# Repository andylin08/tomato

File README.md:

# RGB Pomodoro Timer

This is a pocket Pomodoro timer that displays time, date, and motivational quotes using RGB LEDs, dual OLED screens, and Cherry MX switches, all powered by an ESP32-C3. It’s designed to be compact, functional, and visually engaging.

I made this project because I wanted a fun and personal way to stay focused during work sessions. I’ve always liked the tactile feel of mechanical keys and the glow of addressable LEDs, and this felt like a good way to bring them together into something useful. (Also I have like a bunch of unused stickers and I figured I could use them to decorate the case.)

## images

## Bill of Materials (BOM)

| Item                        | Quantity | Approx. Price | Source |
|-----------------------------|----------|----------------|--------|
| ESP32-C3 DevKitM-1          | 1        | $9.40        | [DigiKey](https://www.digikey.com/en/products/detail/espressif-systems/ESP32-C3-DEVKITM-1U/15198974) |
| SK6812 Mini RGB LEDs (20x minimum)| 6  | $2.34         | [AliExpress](https://www.aliexpress.us/item/3256805007401420.html) |
| Cherry MX Switches          | 4        | $0 (alr have them)  | [AliExpress](https://www.aliexpress.us/item/2255800925392137.html) |
| 0.96" I2C OLED Display      | 2        | $4.64 total   | [AliExpress](https://www.aliexpress.us/item/3256804169233174.html) |
| Passive Buzzer              | 1        | $0 (alr have one) | [AliExpress](https://www.aliexpress.us/item/3256807544525574.html) |
| Battery Holder (AAA or 9V) | 1        | $1.01         | [AliExpress](https://www.aliexpress.us/item/3256805982918007.html) |
| Prototype PCB / Custom PCB | 1        | $26.73 (shipping included)  | JLCPCB |
| Total |0| $44.12 (47.20 w tax) | n/a |

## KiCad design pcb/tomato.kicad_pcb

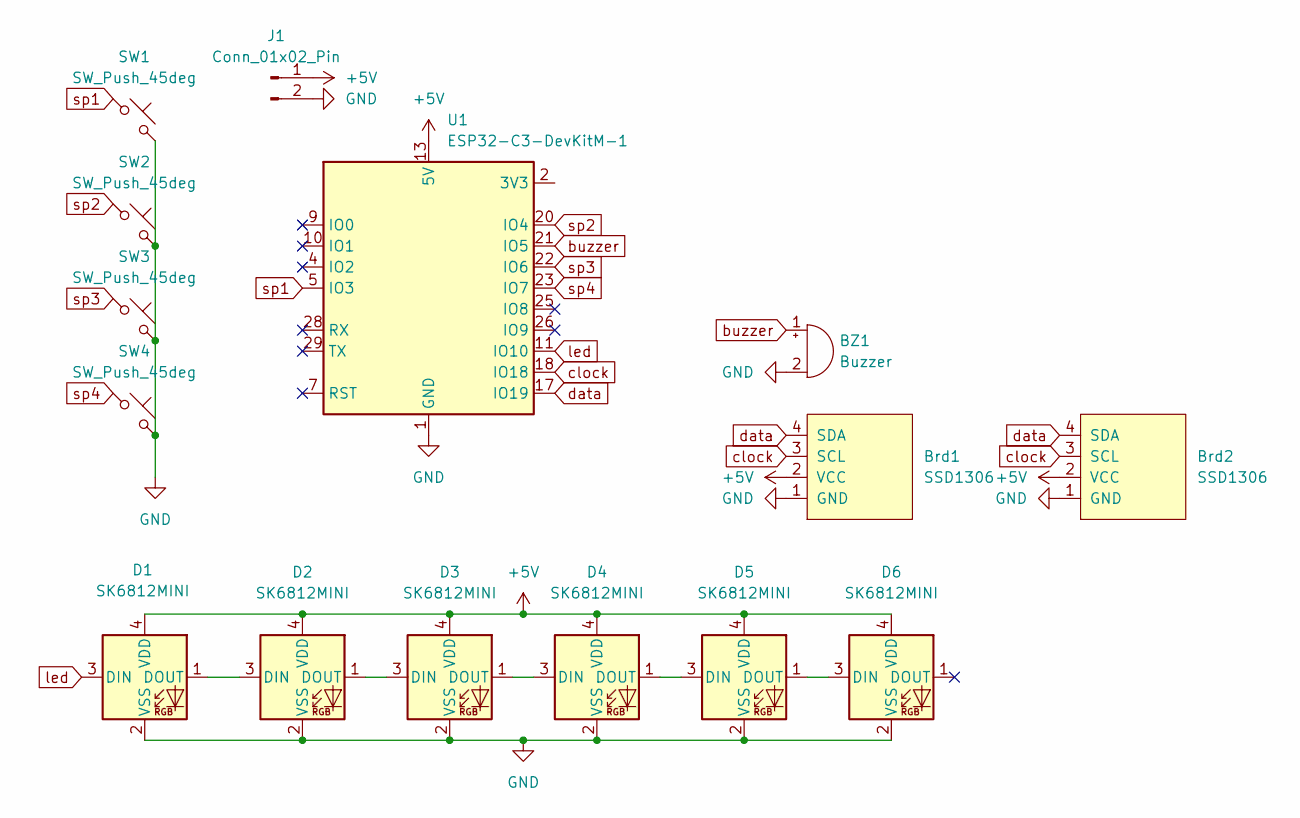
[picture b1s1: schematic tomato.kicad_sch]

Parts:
BZ1: Buzzer; Buzzer_15x7.5RM7.6
Brd1, Brd2: SSD1306; JST_PH_B4B-PH-K_1x04_P2.00mm_Vertical
D1, D2, D3, D4, D5, D6: SK6812MINI; LED_SK6812MINI_PLCC4_3.5x3.5mm_P1.75mm
J1: Conn_01x02_Pin; JST_PH_S2B-PH-K_1x02_P2.00mm_Horizontal
SW1, SW2, SW3, SW4: SW_Push_45deg; SW_Cherry_MX_1.00u_PCB
U1: ESP32-C3-DevKitM-1

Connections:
+5V: Brd1.2 (VCC), Brd2.2 (VCC), D1.4 (VDD), D2.4 (VDD), D3.4 (VDD), D4.4 (VDD), D5.4 (VDD), D6.4 (VDD), J1.1, U1.13 (5V), U1.14 (5V)
GND: BZ1.2 (-), Brd1.1 (GND), Brd2.1 (GND), D1.2 (VSS), D2.2 (VSS), D3.2 (VSS), D4.2 (VSS), D5.2 (VSS), D6.2 (VSS), J1.2, SW1.2, SW2.2, SW3.2, SW4.2, U1.1 (GND), U1.6 (GND), U1.8 (GND), U1.12 (GND), U1.15 (GND), U1.16 (GND), U1.19 (GND), U1.24 (GND), U1.27 (GND), U1.30 (GND)
unnamed: D1.1 (DOUT), D2.3 (DIN)
unnamed: D2.1 (DOUT), D3.3 (DIN)
unnamed: D3.1 (DOUT), D4.3 (DIN)
unnamed: D4.1 (DOUT), D5.3 (DIN)
unnamed: D5.1 (DOUT), D6.3 (DIN)
unnamed: U1.2 (3V3), U1.3 (3V3)
buzzer: BZ1.1 (+), U1.21 (IO5)
clock: Brd1.3 (SCL), Brd2.3 (SCL), U1.18 (IO18)
data: Brd1.4 (SDA), Brd2.4 (SDA), U1.17 (IO19)
led: D1.3 (DIN), U1.11 (IO10)
sp1: SW1.1, U1.5 (IO3)
sp2: SW2.1, U1.20 (IO4)
sp3: SW3.1, U1.22 (IO6)
sp4: SW4.1, U1.23 (IO7)

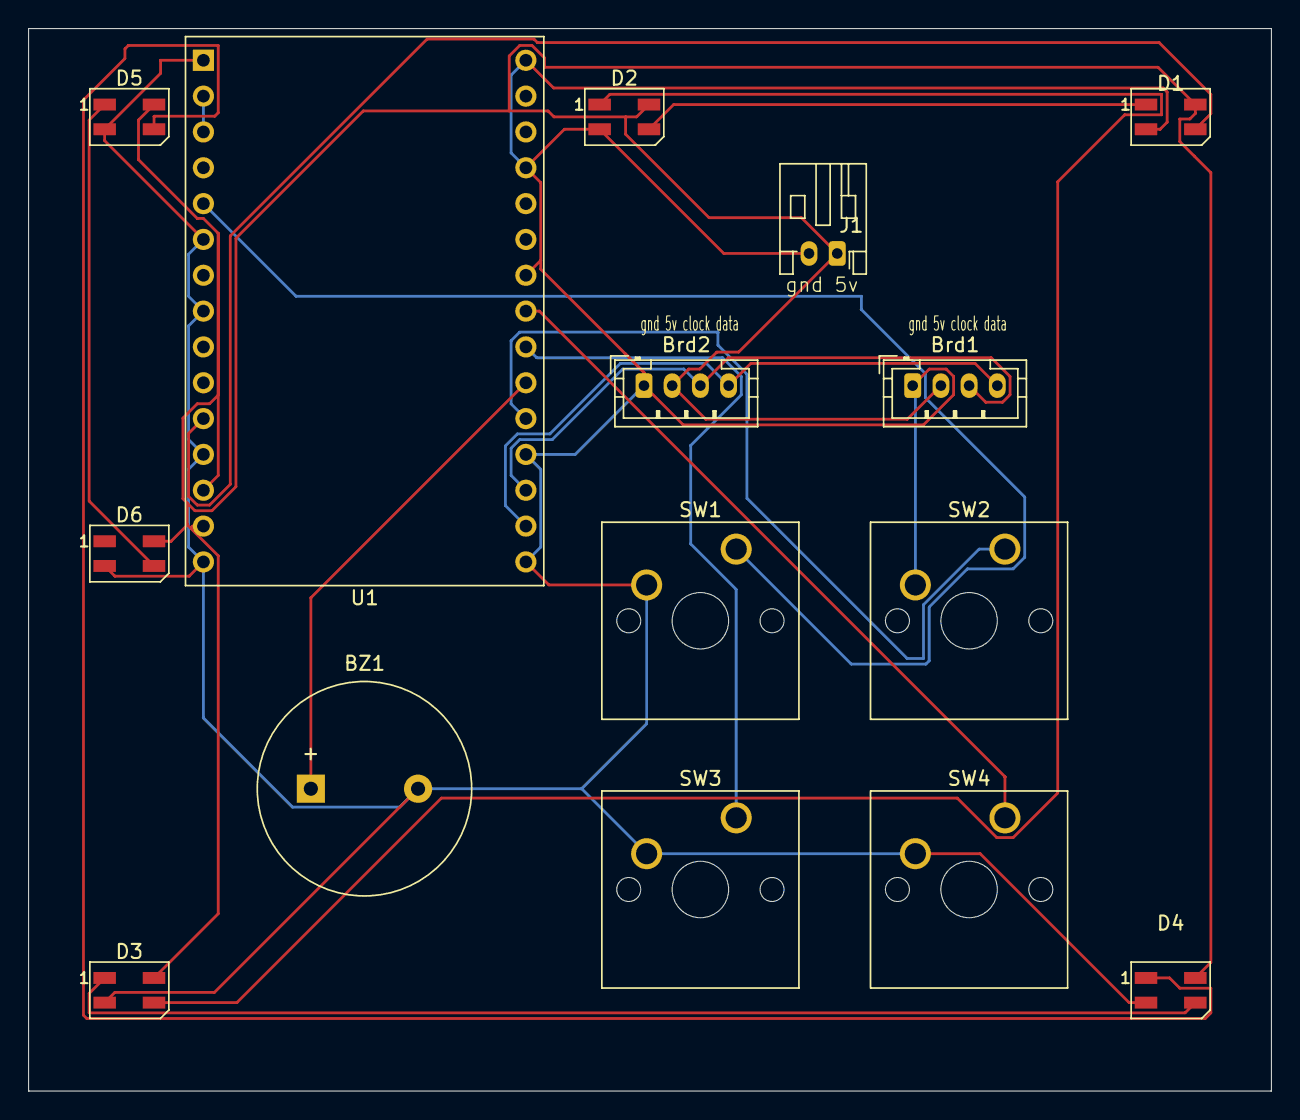
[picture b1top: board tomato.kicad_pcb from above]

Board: 2 copper layers, 88.1 x 75.3 mm, 15 parts (0 on the bottom side), 16 nets.
